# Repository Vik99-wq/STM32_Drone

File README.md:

# STM32_Drone
Custom STM32_Drone Flight Controller and Code

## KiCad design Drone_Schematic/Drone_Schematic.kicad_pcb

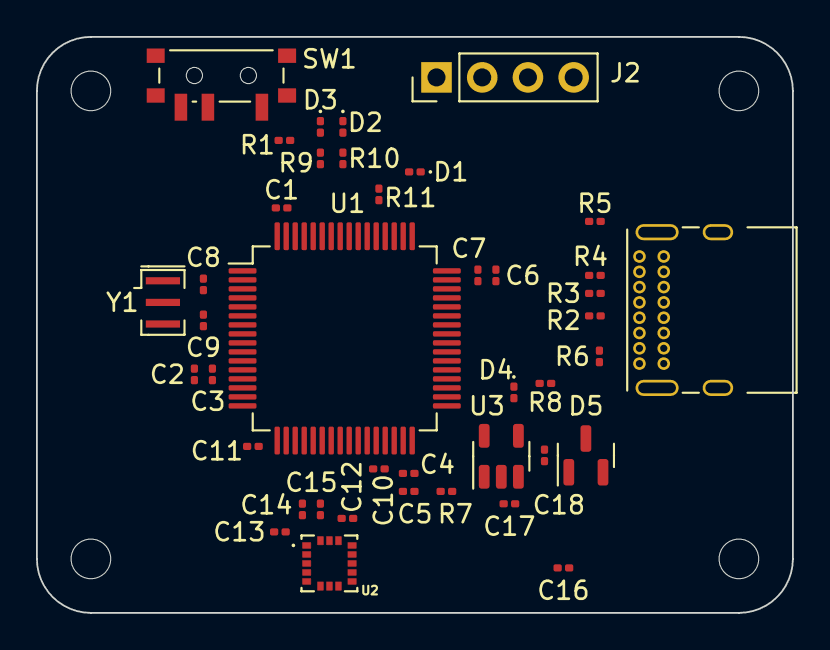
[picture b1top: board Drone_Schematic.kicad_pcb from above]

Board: 2 copper layers, 42.0 x 32.0 mm, 45 parts (0 on the bottom side), 32 nets, no tracks yet.

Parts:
C1, C2, C3, C4, C5, C6, C7, C11: 100nF; C_0201_0603Metric
C8, C9: 56pF; C_0201_0603Metric
C10: 4.7uF; C_0201_0603Metric
C12: 0.47 uF; C_0201_0603Metric
C13: 10 uF; C_0201_0603Metric
C14: 0.1 uF; C_0201_0603Metric
C15: 2.2 uF; C_0201_0603Metric
C16: 22nF; C_0201_0603Metric
C17, C18: 1uF; C_0201_0603Metric
D1: WHITE; LED_0201_0603Metric
D2: GREEN; LED_0201_0603Metric
D3: BLUE; LED_0201_0603Metric
D4: RED; LED_0201_0603Metric
D5: NSVMMBD354LT1G; SOT-23
H1, H2, H3, H4: MountingHole; MountingHole_2.2mm_M2
J1: USB_C_Receptacle_USB2.0; USB_C_Receptacle_GCT_USB4085
J2: Conn_01x04_Male; PinHeader_1x04_P2.54mm_Vertical
R1, R9, R10, R11: 10kΩ; R_0201_0603Metric
R2, R3: 22Ω; R_0201_0603Metric
R4: 1.5KΩ; R_0201_0603Metric
R5, R6: 5.1kΩ; R_0201_0603Metric
R7: 100kΩ; R_0201_0603Metric
R8: 1kΩ; R_0201_0603Metric
SW1: Switch; SW_SPDT_PCM12
U1: STM32F446RETx; LQFP-64_10x10mm_P0.5mm
U2: IAM-20680; PQFN50P300X300X80-16N
U3: RT9193-33GB; SOT-23-5
Y1: 8Mhz; Resonator_SMD_Murata_CSTxExxV-3Pin_3.0x1.1mm

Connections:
+3.3V: C1.2, C2.2, C3.2, C4.2, C5.2, C6.2, C7.2, C13.2, C14.2, C15.2, C18.1, D4.2 (A), J2.4, R4.1, R7.1, SW1.3, U1.1 (VBAT), U1.13 (VDDA), U1.19 (VDD), U1.32 (VDD), U1.48 (VDD), U1.64 (VDD), U2.1 (VDDIO), U2.16 (VDD), U3.4 (VOUT)
/D+: R3.1, U1.45 (PA12)
/D-: R2.2, U1.44 (PA11)
/GYRO_CS: U1.20 (PA4), U2.5 (CS)
/GYRO_INT: U1.9 (PC1), U2.6 (INT)
/GYRO_SDI: U1.23 (PA7), U2.3 (SDA/SDI)
/GYRO_SDO: U1.22 (PA6), U2.4 (SA0/SDO)
/GYRO_SPC: U1.21 (PA5), U2.2 (SCL/SPC)
/LED1: R11.1, U1.56 (PB4)
/LED2: R10.1, U1.57 (PB5)
/LED3: R9.1, U1.58 (PB6)
/SWCLK: J2.2, U1.49 (PA14)
/SWDIO: J2.3, U1.46 (PA13)
GND: C1.1, C2.1, C3.1, C4.1, C5.1, C6.1, C7.1, C8.1, C9.1, C10.2, C11.1, C12.2, C13.1, C14.1, C15.1, C16.2, C17.1, C18.2, D1.1 (K), D2.1 (K), D3.1 (K), J1.A1 (GND), J1.A12 (GND), J1.B1 (GND), J1.B12 (GND), J1.S1 (SHIELD), J2.1, R5.1, R6.1, R8.1, SW1.2, U1.12 (VSSA), U1.18 (VSS), U1.31 (VSS), U1.47 (VSS), U1.63 (VSS), U2.8 (FSYNC), U2.9 (RESV9_1215), U2.10 (RESV9_1215), U2.11 (RESV9_1215), U2.12 (RESV9_1215), U2.13 (GND), U2.15 (RESV9_1215), U3.2 (GND), Y1.2
unnamed: C8.2, U1.5 (PH0), Y1.1
unnamed: C9.2, U1.6 (PH1), Y1.3
unnamed: C10.1, U1.30 (VCAP_1)
unnamed: C11.2, U1.7 (NRST)
unnamed: C12.1, U2.14 (REGOUT)
unnamed: D1.2 (A), R11.2
unnamed: D2.2 (A), R10.2
unnamed: D3.2 (A), R9.2
unnamed: D4.1 (K), R8.2
unnamed: C17.2, D5.1 (A), U3.3 (VIN)
unnamed: J1.A5 (CC1), R6.2
unnamed: J1.A6 (D+), J1.B6 (D+), R3.2, R4.2
unnamed: J1.A7 (D-), J1.B7 (D-), R2.1
unnamed: J1.B5 (CC2), R5.2
unnamed: R1.1, U1.60 (BOOT0)
unnamed: R1.2, SW1.1
unnamed: R7.2, U3.1 (EN)
VBUS: D5.2 (K), J1.A4 (VBUS), J1.A9 (VBUS), J1.B4 (VBUS), J1.B9 (VBUS)

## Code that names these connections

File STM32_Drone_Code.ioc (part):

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Mcu.Name=STM32F446R(C-E)Tx
Mcu.Package=LQFP64
Mcu.UserName=STM32F446RETx
PA11.Mode=Device_Only
PA11.Signal=USB_OTG_FS_DM
PA12.Mode=Device_Only
PA12.Signal=USB_OTG_FS_DP
PA13.GPIOParameters=GPIO_Label
PA13.GPIO_Label=TMS
PA13.Mode=Trace_Asynchronous_SW
PA13.Signal=SYS_JTMS-SWDIO
PA14.GPIOParameters=GPIO_Label
PA14.GPIO_Label=TCK
PA14.Mode=Trace_Asynchronous_SW
PA14.Signal=SYS_JTCK-SWCLK
PA2.GPIOParameters=GPIO_Label
PA2.GPIO_Label=USART_TX
PA2.Mode=Asynchronous
PA2.Signal=USART2_TX
PA3.GPIOParameters=GPIO_Label
PA3.GPIO_Label=USART_RX
PA3.Mode=Asynchronous
PA3.Signal=USART2_RX
PA4.GPIOParameters=GPIO_Label
PA4.GPIO_Label=IMU_NCS
PA4.Signal=GPIO_Output
PA5.Mode=Full_Duplex_Master
PA5.Signal=SPI1_SCK
PA6.Mode=Full_Duplex_Master
PA6.Signal=SPI1_MISO
PA7.Mode=Full_Duplex_Master
PA7.Signal=SPI1_MOSI
PB10.Signal=S_TIM2_CH3
PB2.Signal=S_TIM2_CH4
PB3.Mode=Trace_Asynchronous_SW
PB3.Signal=SYS_JTDO-SWO
PB4.GPIOParameters=GPIO_Label
PB4.GPIO_Label=LED1
PB4.Signal=GPIO_Output
PB5.GPIOParameters=GPIO_Label
PB5.GPIO_Label=LED2
PB5.Signal=GPIO_Output
PB6.GPIOParameters=GPIO_Label
PB6.GPIO_Label=LED3
PB6.Signal=GPIO_Output
PB8.Signal=S_TIM2_CH1_ETR
PB9.Signal=S_TIM2_CH2
PC1.GPIOParameters=GPIO_Label
PC1.GPIO_Label=Gyro_Interrupt
PC1.Signal=GPIO_Output
PC13.GPIOParameters=GPIO_Label,GPIO_ModeDefaultEXTI
PC13.GPIO_Label=B1 [Blue PushButton]
PC13.GPIO_ModeDefaultEXTI=GPIO_MODE_IT_FALLING
PC13.Signal=GPXTI13
PH0-OSC_IN.Mode=HSE-External-Oscillator
PH0-OSC_IN.Signal=RCC_OSC_IN
PH1-OSC_OUT.Mode=HSE-External-Oscillator
PH1-OSC_OUT.Signal=RCC_OSC_OUT
RCC.HSE_VALUE=8000000
RCC.SYSCLKFreq_VALUE=168000000
RCC.SYSCLKSource=RCC_SYSCLKSOURCE_PLLCLK
board=NUCLEO-F446RE
boardIOC=true

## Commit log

2022-07-19 Kicad Schematic
